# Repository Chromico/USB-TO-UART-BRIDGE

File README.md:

# USB TO UART BRIDGE REV1

An open source USB to UART converter based on the CH340C IC and designed in KiCad by Tecknologg. The board design and schematic is open source so do whatever you wish with it :)

My website: https://tecknologg.website

# Dimensions 

# Assembled board

# Documentation
You can get the official documentation here: https://github.com/Chromico/USB-TO-UART-BRIDGE/blob/master/docs/CH340C%20USB%20TO%20UART%20BRIDGE%20Documentation.pdf

# Certification
As from 2020, this project is open source hardware certified.

# Contact

Need to contact me ? Just send me an email at nathan@tecknologg.website or tecknologg@gmail.com

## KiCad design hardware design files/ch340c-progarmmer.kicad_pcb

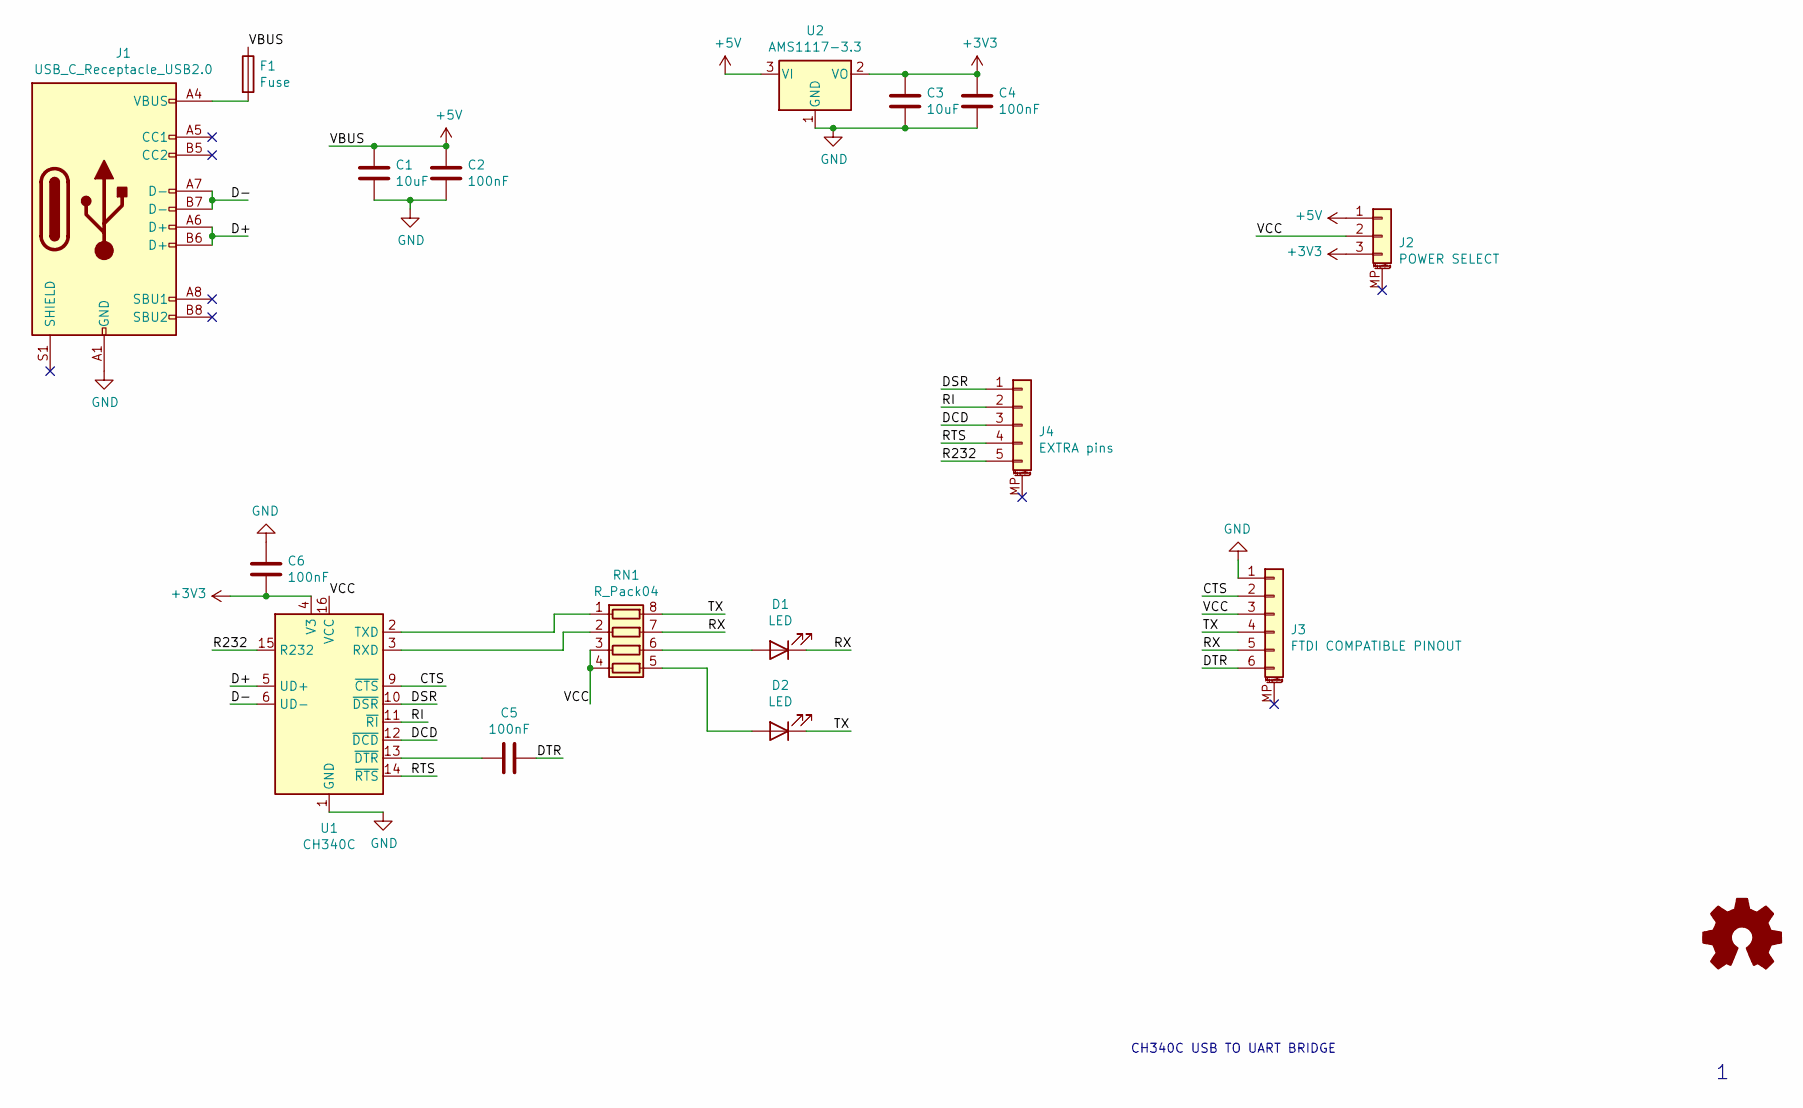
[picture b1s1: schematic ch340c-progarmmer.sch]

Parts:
C1, C3: 10uF
C2, C4, C5, C6: 100nF
D1, D2: LED
F1: Fuse
J1: USB_C_Receptacle_USB2.0
J2: POWER SELECT
J3: FTDI COMPATIBLE PINOUT
J4: EXTRA pins
RN1: R_Pack04
U1: CH340C; SOIC-16_3.9x9.9mm_P1.27mm
U2: AMS1117-3.3; SOT-223-3_TabPin2

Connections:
+3V3: C3.1, C4.1, C6.2, J2.3, U1.4 (V3), U2.2 (VO)
+5V: C1.1, C2.1, F1.1, J2.1, U2.3 (VI)
/CTS: J3.2, U1.9 (~CTS)
/D+: J1.A6 (D+), J1.B6 (D+), U1.5 (UD+)
/D-: J1.A7 (D-), J1.B7 (D-), U1.6 (UD-)
/DCD: J4.3, U1.12 (~DCD)
/DSR: J4.1, U1.10 (~DSR)
/DTR: C5.1, J3.6
/R232: J4.5, U1.15 (R232)
/RI: J4.2, U1.11 (~RI)
/RTS: J4.4, U1.14 (~RTS)
/RX: D1.1 (K), J3.5, RN1.7 (R2.2)
/TX: D2.1 (K), J3.4, RN1.8 (R1.2)
/VCC: J2.2, J3.3, RN1.3 (R3.1), RN1.4 (R4.1), U1.16 (VCC)
GND: C1.2, C2.2, C3.2, C4.2, C6.1, J1.A1 (GND), J1.A12 (GND), J1.B1 (GND), J1.B12 (GND), J3.1, U1.1 (GND), U2.1 (GND)
unnamed: C5.2, U1.13 (~DTR)
unnamed: D1.2 (A), RN1.6 (R3.2)
unnamed: D2.2 (A), RN1.5 (R4.2)
unnamed: F1.2, J1.A4 (VBUS), J1.A9 (VBUS), J1.B4 (VBUS), J1.B9 (VBUS)
unnamed: RN1.1 (R1.1), U1.2 (TXD)
unnamed: RN1.2 (R2.1), U1.3 (RXD)

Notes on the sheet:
CH340C USB TO UART BRIDGE

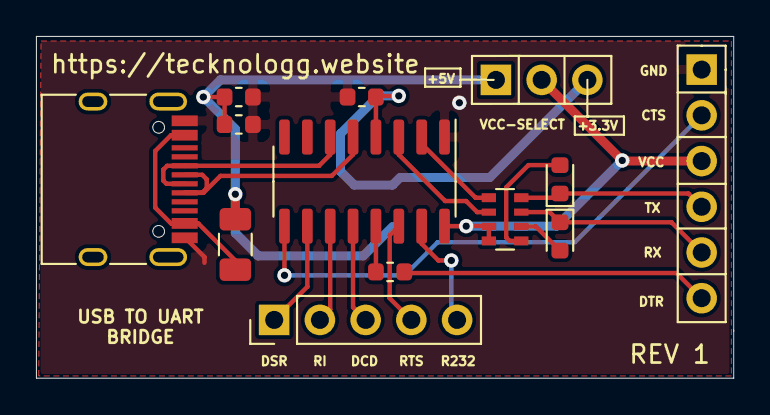
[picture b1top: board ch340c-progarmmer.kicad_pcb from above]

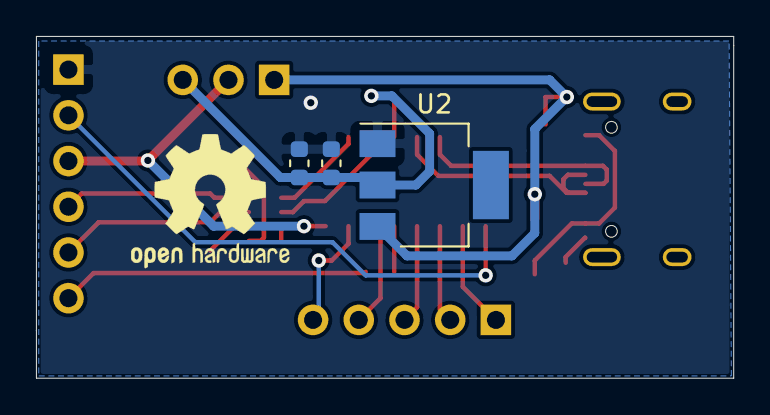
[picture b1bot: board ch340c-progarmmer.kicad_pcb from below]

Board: 2 copper layers, 38.7 x 19.0 mm, 16 parts (3 on the bottom side), 21 nets.

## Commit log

2020-08-08 Update LICENSE
2020-08-15 [ImgBot] Optimize images
    *Total -- 407.59kb -> 346.77kb (14.92%)
    /pics/dimensions.png -- 102.73kb -> 57.99kb (43.55%)
    /pics/oshw-mu000002.png -- 5.79kb -> 4.94kb (14.79%)
    /pics/final2.jpg -- 160.75kb -> 151.42kb (5.8%)
    /pics/final1.jpg -- 138.31kb -> 132.42kb (4.26%)
